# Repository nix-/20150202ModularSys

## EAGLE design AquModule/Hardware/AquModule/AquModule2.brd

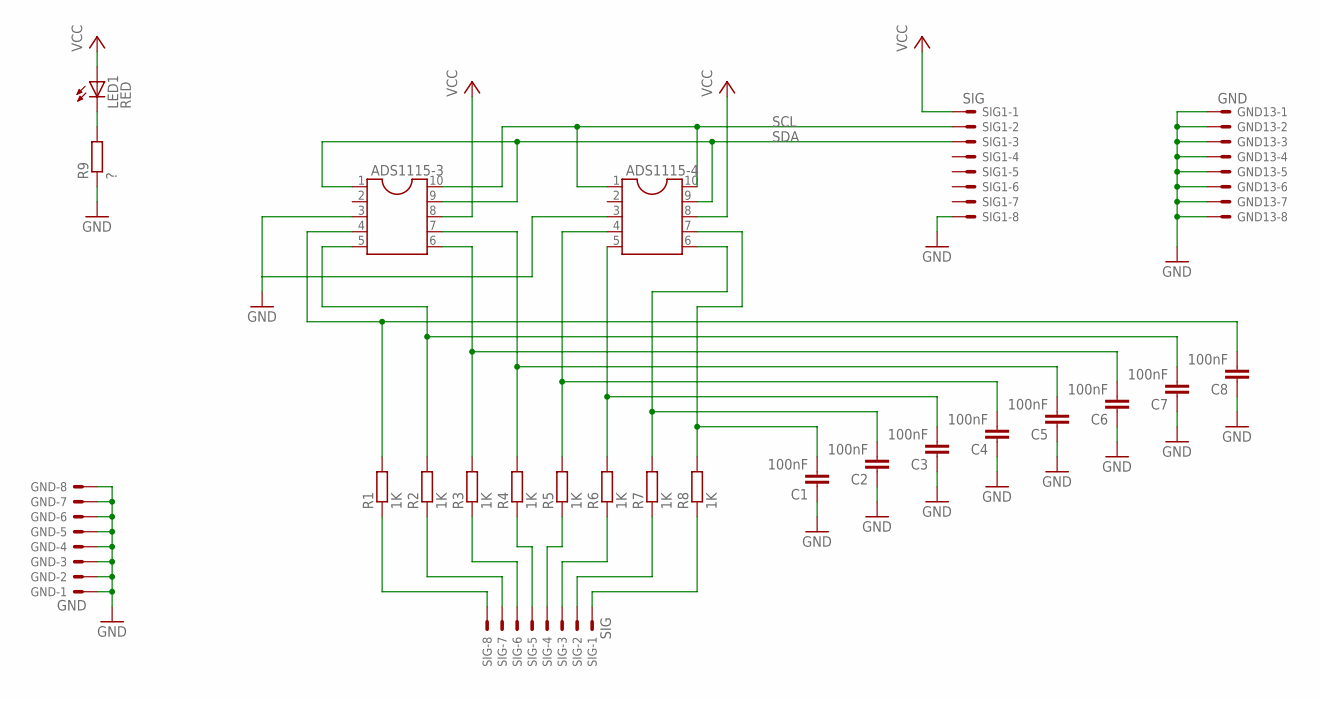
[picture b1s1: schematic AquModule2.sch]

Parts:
ADS1115-3, ADS1115-4: DIL10
C1, C2, C3, C4, C5, C6, C7, C8: 100nF; C1206
GND, GND13: GND; 15-91-08
LED1: RED; LED_LD260
R1, R2, R3, R4, R5, R6, R7, R8: 1K; R1206
R9: ?; 0207/2V
SIG, SIG1: SIG; 15-91-08

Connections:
GND: ADS1115-3.3, ADS1115-4.3, C1.1, C2.1, C3.1, C4.1, C5.1, C6.1, C7.1, C8.1, GND.1, GND.2, GND.3, GND.4, GND.5, GND.6, GND.7, GND.8, GND13.1, GND13.2, GND13.3, GND13.4, GND13.5, GND13.6, GND13.7, GND13.8, R9.1, SIG1.8
unnamed: ADS1115-3.4, C8.2, R1.2
unnamed: ADS1115-3.5, C7.2, R2.2
unnamed: ADS1115-3.6, C6.2, R3.2
unnamed: ADS1115-3.7, C5.2, R4.2
unnamed: ADS1115-4.4, C4.2, R5.2
unnamed: ADS1115-4.5, C3.2, R6.2
unnamed: ADS1115-4.6, C2.2, R7.2
unnamed: ADS1115-4.7, C1.2, R8.2
unnamed: R1.1, SIG.8
unnamed: R2.1, SIG.7
unnamed: R3.1, SIG.6
unnamed: R4.1, SIG.5
unnamed: R5.1, SIG.4
unnamed: R6.1, SIG.3
unnamed: R7.1, SIG.2
unnamed: R8.1, SIG.1
unnamed: LED1.K (C), R9.2
SCL: ADS1115-3.10, ADS1115-4.1, ADS1115-4.10, SIG1.2
SDA: ADS1115-3.1, ADS1115-3.9, ADS1115-4.9, SIG1.3
VCC: ADS1115-3.8, ADS1115-4.8, LED1.A, SIG1.1

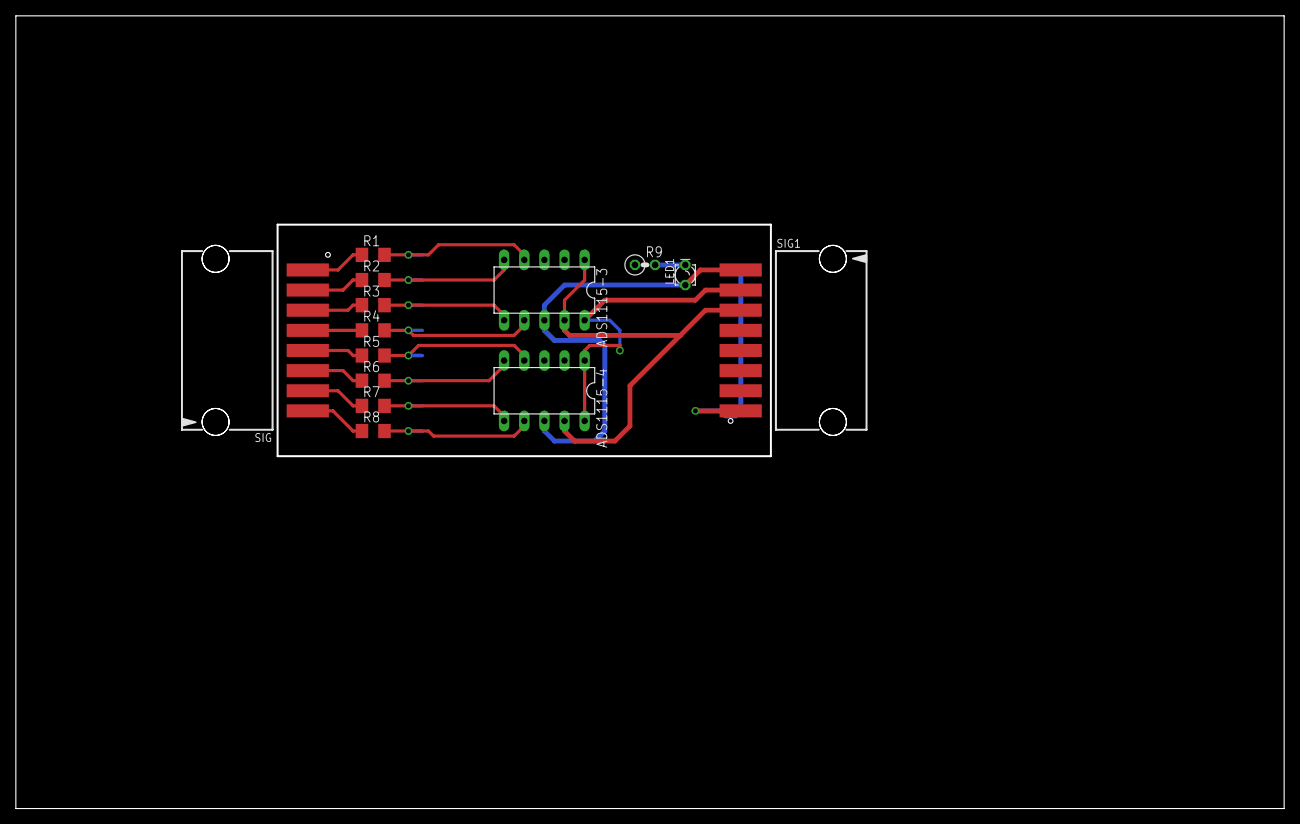
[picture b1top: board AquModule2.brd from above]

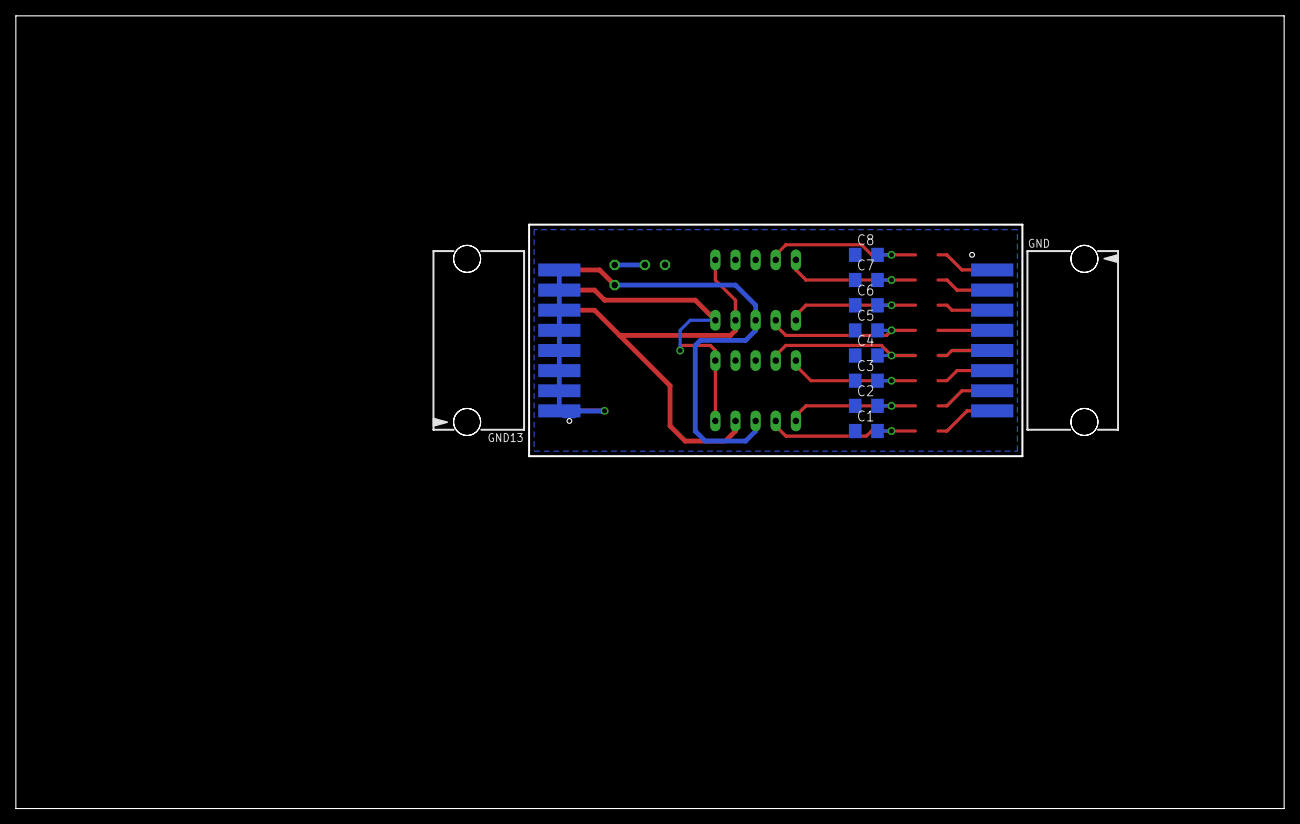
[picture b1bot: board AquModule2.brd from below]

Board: 2 copper layers, 160.0 x 100.0 mm, 24 parts (10 on the bottom side), 21 nets.

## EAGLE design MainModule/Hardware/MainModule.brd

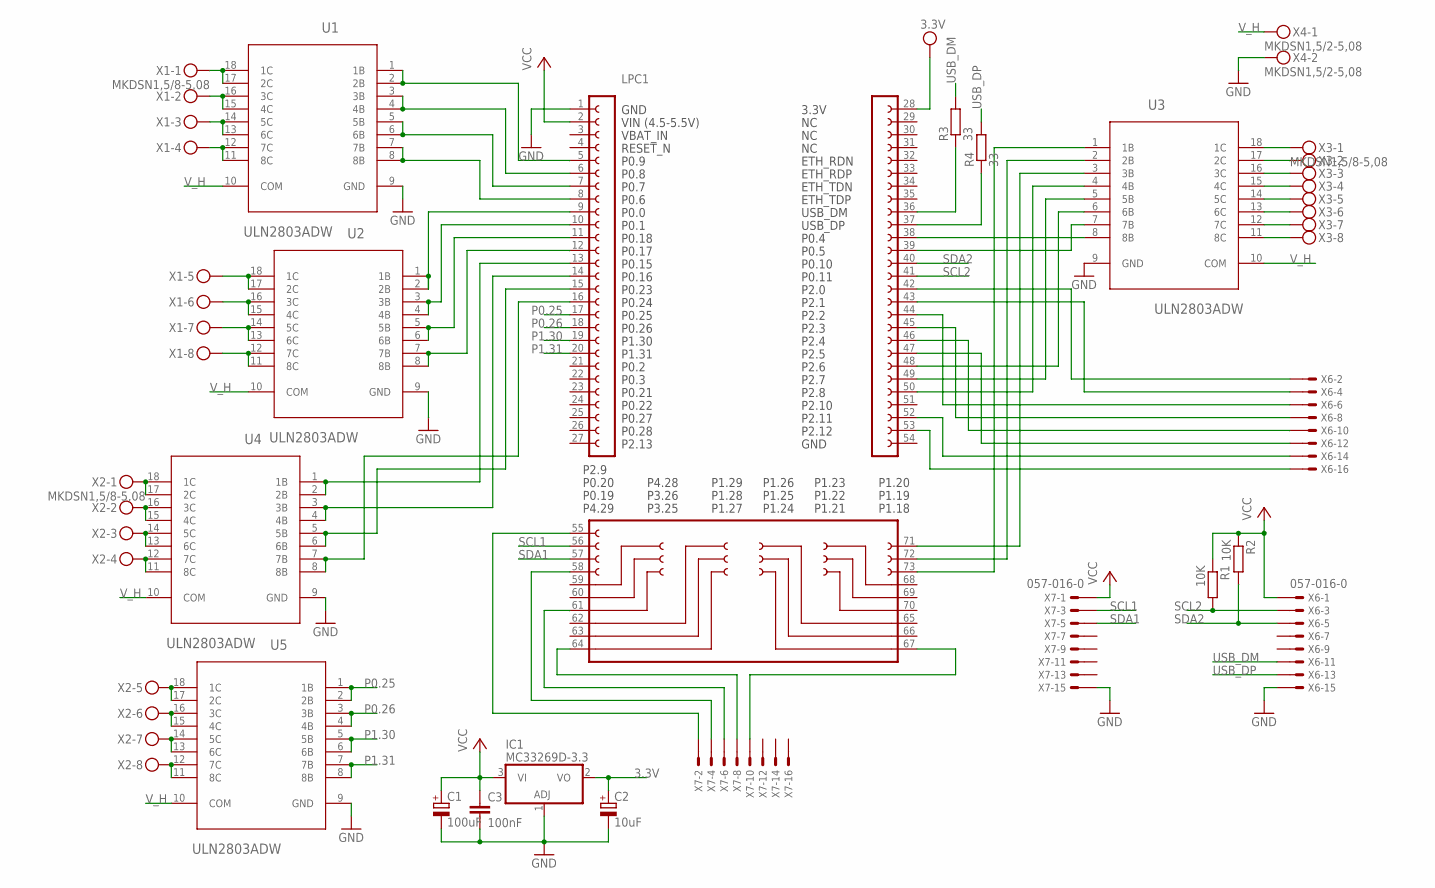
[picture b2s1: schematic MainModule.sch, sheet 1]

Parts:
C1: 100uF; 153CLV-0810
C2: 10uF; 153CLV-0810
C3: 100nF; C0805
IC1: MC33269D-3.3; DPACK
LPC1: LPCXPRESSO_LPC1769
R1, R2: 10K; MINI_MELF-0204W
R3, R4: 33; M3216
U1, U2, U3, U4, U5: ULN2803ADW; SOIC127P1030X265-18N
X1, X2, X3: MKDSN1,5/8-5,08
X4: MKDSN1,5/2-5,08
X6, X7: 057-016-0

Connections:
3.3V: C2.+, IC1.2 (VO), LPC1.28
GND: C1.-, C2.-, C3.2, IC1.1 (ADJ), LPC1.1, U1.9 (GND), U2.9 (GND), U3.9 (GND), U4.9 (GND), U5.9 (GND), X4.2, X6.15, X7.15; also elsewhere on the board
unnamed: U5.17 (2C), U5.18 (1C), X2.5
unnamed: U5.15 (4C), U5.16 (3C), X2.6
unnamed: U2.17 (2C), U2.18 (1C), X1.5
unnamed: U5.13 (6C), U5.14 (5C), X2.7
unnamed: LPC1.38, U3.8 (8B)
unnamed: LPC1.39, U3.7 (7B)
unnamed: LPC1.48, U3.6 (6B)
unnamed: LPC1.49, U3.5 (5B)
unnamed: LPC1.50, U3.4 (4B)
unnamed: U1.15 (4C), U1.16 (3C), X1.2
unnamed: U1.13 (6C), U1.14 (5C), X1.3
unnamed: LPC1.73, U3.1 (1B)
unnamed: U1.17 (2C), U1.18 (1C), X1.1
unnamed: U1.11 (8C), U1.12 (7C), X1.4
unnamed: U5.11 (8C), U5.12 (7C), X2.8
unnamed: U2.15 (4C), U2.16 (3C), X1.6
unnamed: U2.13 (6C), U2.14 (5C), X1.7
unnamed: U2.11 (8C), U2.12 (7C), X1.8
unnamed: U4.17 (2C), U4.18 (1C), X2.1
unnamed: U4.15 (4C), U4.16 (3C), X2.2
unnamed: U4.13 (6C), U4.14 (5C), X2.3
unnamed: U4.11 (8C), U4.12 (7C), X2.4
unnamed: U3.18 (1C), X3.1
unnamed: U3.17 (2C), X3.2
unnamed: U3.16 (3C), X3.3
unnamed: U3.15 (4C), X3.4
unnamed: U3.14 (5C), X3.5
unnamed: U3.13 (6C), X3.6
unnamed: U3.12 (7C), X3.7
unnamed: U3.11 (8C), X3.8
unnamed: LPC1.42, X6.2
unnamed: LPC1.47, X6.12
unnamed: LPC1.46, X6.10
unnamed: LPC1.45, X6.8
unnamed: LPC1.44, X6.6
unnamed: LPC1.53, X6.16
unnamed: LPC1.52, X6.14
unnamed: LPC1.43, X6.4
unnamed: LPC1.67, X7.10
unnamed: LPC1.64, X7.8
unnamed: LPC1.61, X7.6
unnamed: LPC1.58, X7.4
unnamed: LPC1.55, X7.2
unnamed: LPC1.36, R3.1
unnamed: LPC1.37, R4.1
unnamed: LPC1.72, U3.2 (2B)
unnamed: LPC1.71, U3.3 (3B)
OUT1: LPC1.5, U1.1 (1B), U1.2 (2B); also elsewhere on the board
OUT2: LPC1.6, U1.3 (3B), U1.4 (4B); also elsewhere on the board
OUT3: LPC1.7, U1.5 (5B), U1.6 (6B); also elsewhere on the board
OUT4: LPC1.8, U1.7 (7B), U1.8 (8B); also elsewhere on the board
OUT5: LPC1.9, U2.1 (1B), U2.2 (2B); also elsewhere on the board
OUT6: LPC1.10, U2.3 (3B), U2.4 (4B); also elsewhere on the board
OUT7: LPC1.11, U2.5 (5B), U2.6 (6B); also elsewhere on the board
OUT8: LPC1.12, U2.7 (7B), U2.8 (8B); also elsewhere on the board
OUT9: LPC1.13, U4.1 (1B), U4.2 (2B); also elsewhere on the board
OUT10: LPC1.14, U4.3 (3B), U4.4 (4B); also elsewhere on the board
OUT11: LPC1.15, U4.5 (5B), U4.6 (6B); also elsewhere on the board
OUT12: LPC1.16, U4.7 (7B), U4.8 (8B); also elsewhere on the board
P0.25: LPC1.17, U5.1 (1B), U5.2 (2B); also elsewhere on the board
P0.26: LPC1.18, U5.3 (3B), U5.4 (4B); also elsewhere on the board
P1.30: LPC1.19, U5.5 (5B), U5.6 (6B); also elsewhere on the board
P1.31: LPC1.20, U5.7 (7B), U5.8 (8B); also elsewhere on the board
SCL1: LPC1.56, X7.3
SCL2: LPC1.41, R1.2, X6.3
SDA1: LPC1.57, X7.5
SDA2: LPC1.40, R2.2, X6.5
USB_DM: R3.2, X6.11
USB_DP: R4.2, X6.13
VCC: C1.+, C3.1, IC1.3 (VI), LPC1.2, R1.1, R2.1, X6.1, X7.1
V_H: U1.10 (COM), U2.10 (COM), U3.10 (COM), U4.10 (COM), U5.10 (COM), X4.1

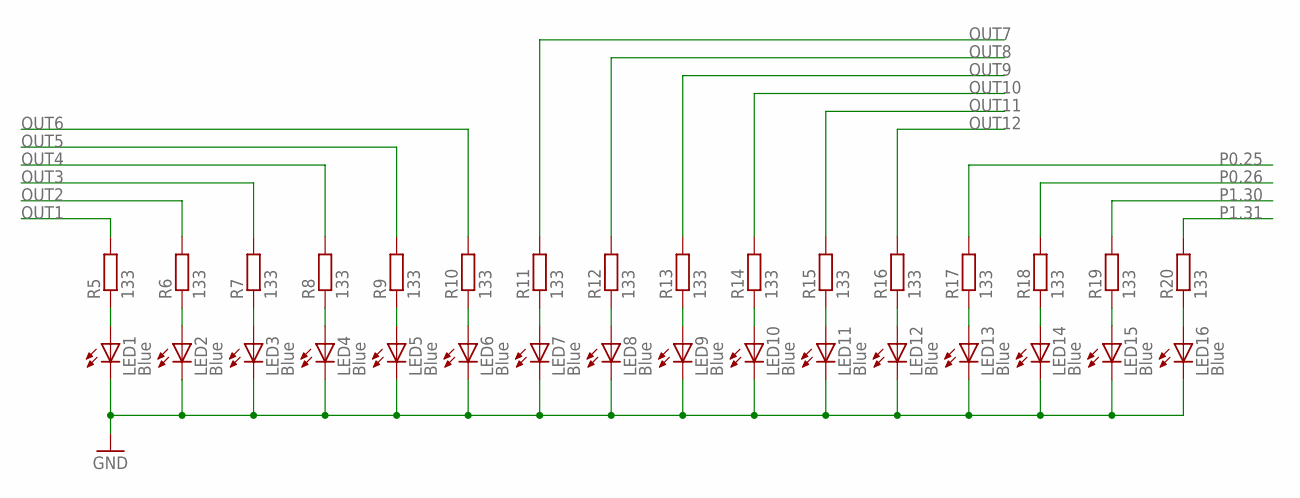
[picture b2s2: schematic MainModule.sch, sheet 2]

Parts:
LED1, LED2, LED3, LED4, LED5, LED6, LED7, LED8, LED9, LED10, LED11, LED12, LED13, LED14, LED15, LED16: Blue; CHIPLED_0805
R5, R6, R7, R8, R9, R10, R11, R12, R13, R14, R15, R16, R17, R18, R19, R20: 133; R1206W

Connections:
GND: LED1.C, LED2.C, LED3.C, LED4.C, LED5.C, LED6.C, LED7.C, LED8.C, LED9.C, LED10.C, LED11.C, LED12.C, LED13.C, LED14.C, LED15.C, LED16.C; also elsewhere on the board
unnamed: LED15.A, R19.1
unnamed: LED13.A, R17.1
unnamed: LED14.A, R18.1
unnamed: LED16.A, R20.1
unnamed: LED1.A, R5.1
unnamed: LED2.A, R6.1
unnamed: LED3.A, R7.1
unnamed: LED4.A, R8.1
unnamed: LED5.A, R9.1
unnamed: LED6.A, R10.1
unnamed: LED7.A, R11.1
unnamed: LED8.A, R12.1
unnamed: LED9.A, R13.1
unnamed: LED10.A, R14.1
unnamed: LED11.A, R15.1
unnamed: LED12.A, R16.1
OUT1: R5.2; also elsewhere on the board
OUT2: R6.2; also elsewhere on the board
OUT3: R7.2; also elsewhere on the board
OUT4: R8.2; also elsewhere on the board
OUT5: R9.2; also elsewhere on the board
OUT6: R10.2; also elsewhere on the board
OUT7: R11.2; also elsewhere on the board
OUT8: R12.2; also elsewhere on the board
OUT9: R13.2; also elsewhere on the board
OUT10: R14.2; also elsewhere on the board
OUT11: R15.2; also elsewhere on the board
OUT12: R16.2; also elsewhere on the board
P0.25: R17.2; also elsewhere on the board
P0.26: R18.2; also elsewhere on the board
P1.30: R19.2; also elsewhere on the board
P1.31: R20.2; also elsewhere on the board

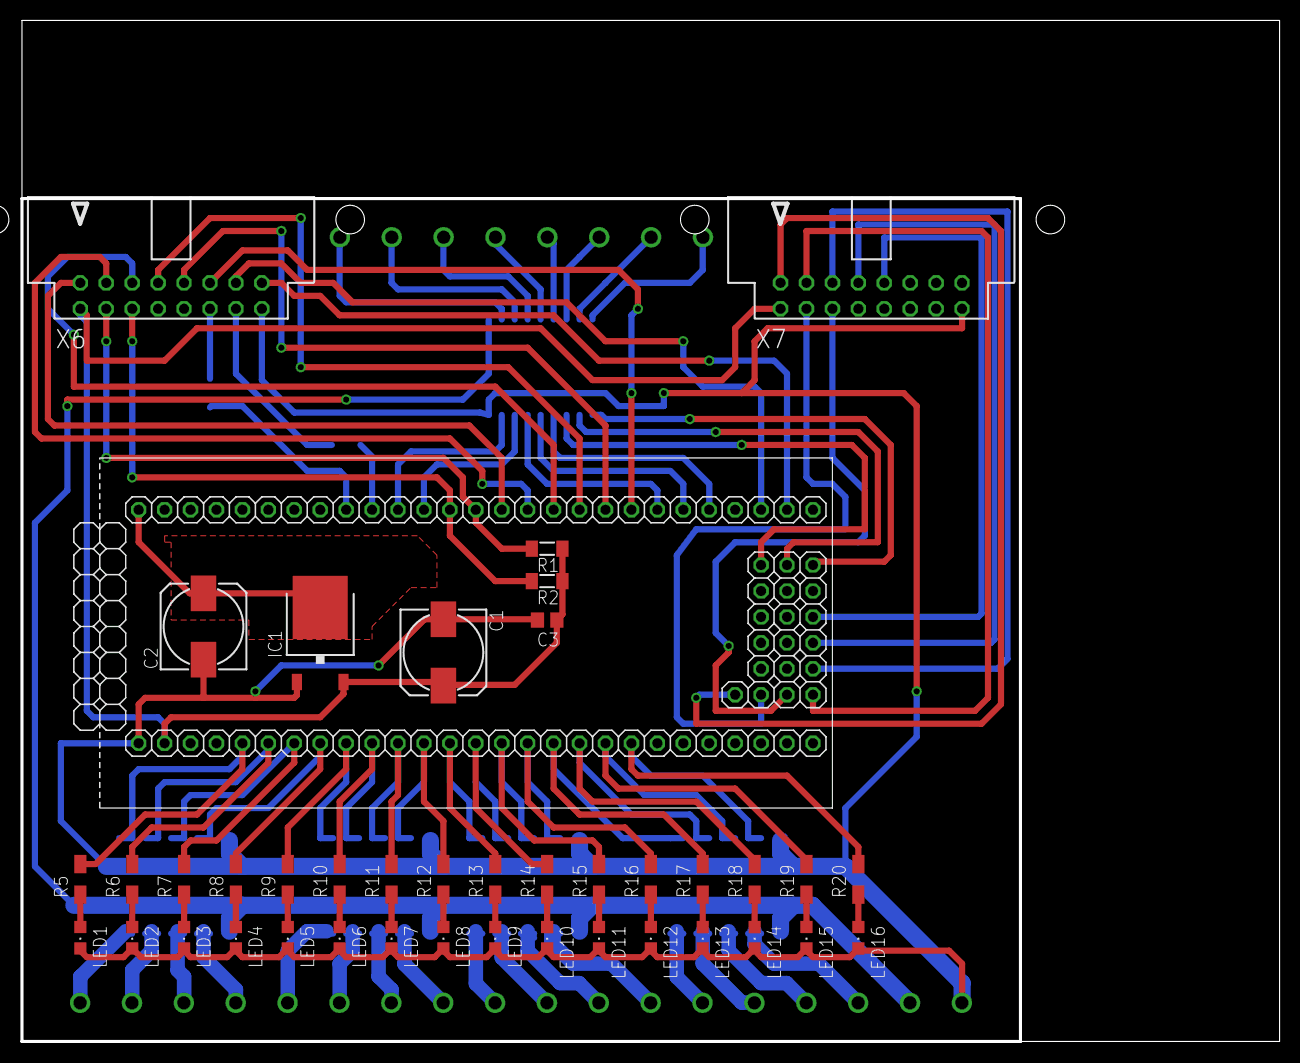
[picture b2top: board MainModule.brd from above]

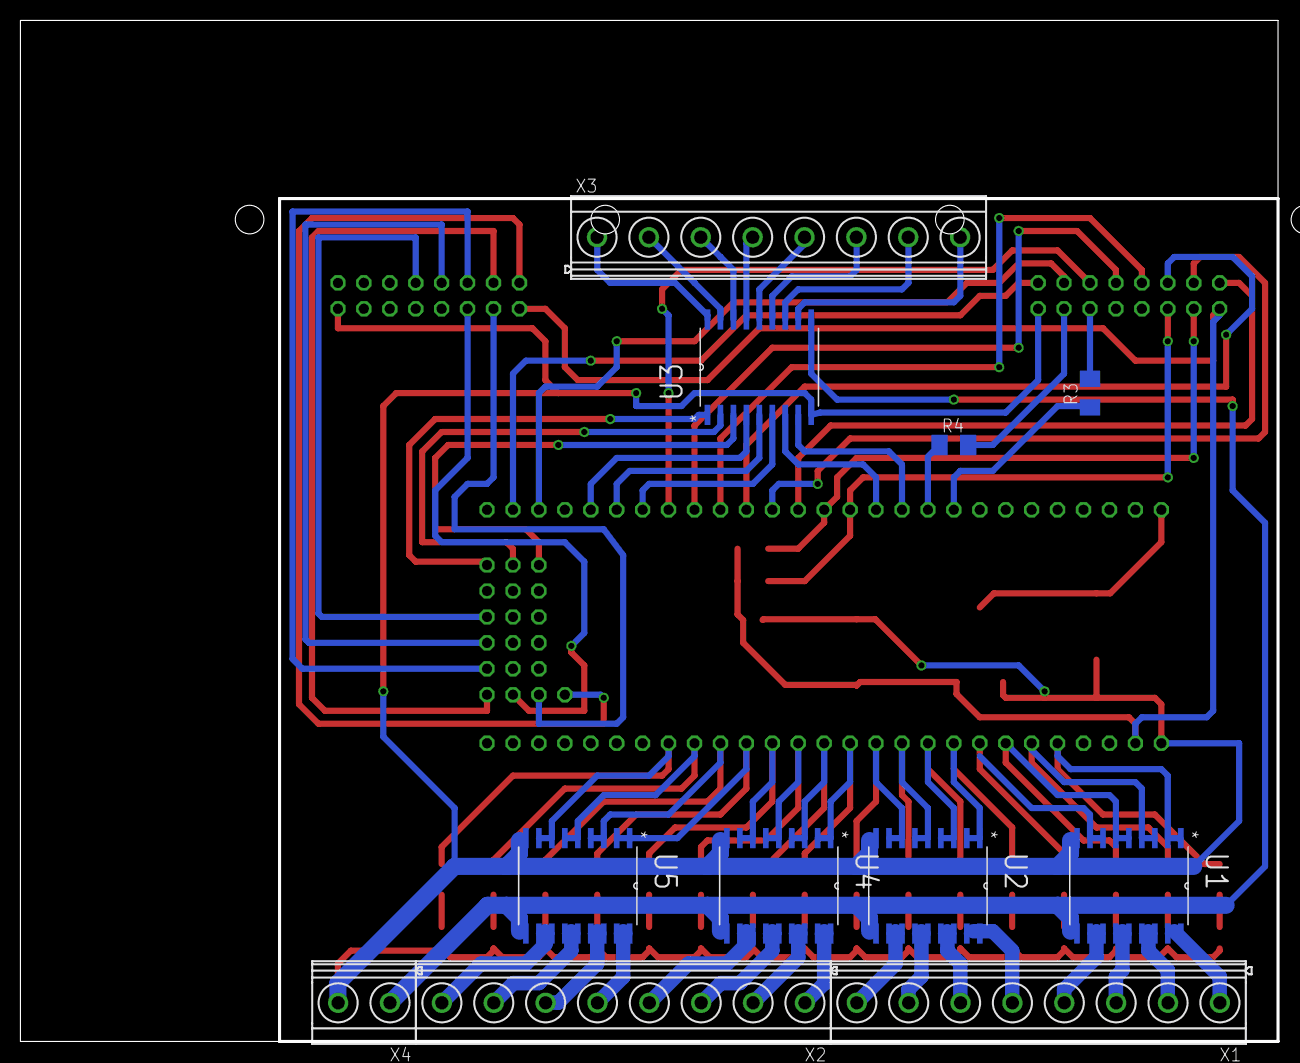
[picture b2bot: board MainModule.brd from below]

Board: 2 copper layers, 123.2 x 100.0 mm, 52 parts (11 on the bottom side), 89 nets.

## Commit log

2015-02-02 Added PCB project files
2015-02-02 Wired all the components and made first PCB wiring
2015-02-03 PCB design for module 1 - Ready
2015-02-04 PCB ADD0 and ADD1 ready
2015-02-05 Aqu Module 2 PCB - Ready
2015-02-05 Eagle project is created.
2015-02-05 Added Eagle library for LPC1769 board
2015-02-06 start of design
2015-02-09 Added Project file for board and ULN2803 library
2015-02-09 80% of the PCB design is ready.
2015-02-10 95% of PCB design is ready. (Added linear regulator)
2015-02-11 99% of PCB design ready. Linear voltage regulator implementation ready.
2015-02-19 Reduce number of outputs and increase power of each of them.
2015-02-26 Zgolemuvanje na vodovit na izleznata strana
2015-02-27 Dodadeni LED za signalizacija na aktiven izlez
2015-02-27 Dodadeni fajlovi za vtoriot modul
